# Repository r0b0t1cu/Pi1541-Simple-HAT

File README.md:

# Pi1541-Simple-HAT

An open-source Raspberry Pi HAT for the [Pi1541](https://github.com/pi1541/Pi1541) project — a cycle-exact emulator of the Commodore 1541 floppy disk drive. This board provides a clean, simple way to build a standalone Pi1541 unit with buttons, display, buzzer, and IEC connectivity, without needing to hand-wire everything on a breadboard.

---

## Overview

Pi1541 turns a Raspberry Pi into a hardware-accurate 1541 emulator that loads `.d64`, `.g64`, `.nib`, and other disk image formats from an SD card. This HAT breaks out everything you need onto a single board that sits directly on top of a Raspberry Pi 3B+.

The design is intentionally minimal — no SMD components beyond the connectors and passives, uses a widely available logic level converter module, and gives you flexibility on the IEC connector (DIN-6 socket or plain pin header, your choice).

---

## Features

- Designed as a standard 40-pin Raspberry Pi HAT
- Bidirectional logic level shifting (3.3V ↔ 5V) for the IEC bus
- Two IEC footprints: DIN-6 connector **or** pin header — populate whichever suits your build
- I2C connector for SSD1306 128×64 OLED display
- 5 navigation buttons: Select/Start, Up, Down, Exit Folder, Insert
- Reset button
- PWR and ACT indicator LEDs with current-limiting resistors
- Passive buzzer with enable/disable jumper (JP1)
- Voltage selector jumper (JP2): +5V or +3.3V for the display
- 4 mounting holes

---

## Hardware

### Bill of Materials

| Ref | Qty | Component | Description |
|-----|-----|-----------|-------------|
| U1 | 1 | SparkFun BOB-12009 (or equivalent) | Bidirectional logic level converter, BSS138-based, 4-channel |
| J1 | 1 | 40-pin female GPIO header | Standard 2.54mm pitch Raspberry Pi header |
| J3 | 1 | DIN-6 female socket **or** 6-pin header | IEC bus connector (primary) |
| J4 | 1 | DIN-6 female socket **or** 6-pin header | IEC bus connector (secondary footprint, same bus) |
| CN1 | 1 | 4-pin header | I2C display connector (GND, VCC, SCL, SDA) |
| SW1–SW5 | 5 | Tactile push button | Navigation: Select/Start, Up, Down, Exit Folder, Insert |
| SW6 | 1 | Tactile push button | Reset |
| LS1 | 1 | Passive buzzer | 5V passive buzzer |
| D1 | 1 | LED | ACT indicator |
| D2 | 1 | LED | PWR indicator |
| R1, R2 | 2 | Resistor | LED current limiting (value depends on LED and supply voltage) |
| JP1 | 1 | 2-pin jumper | Buzzer enable/disable |
| JP2 | 1 | 3-pin jumper | Voltage selector jumper (JP2): +5V or +3.3V for the display |

> **Note on IEC connectors:** J3 and J4 share the same electrical connection. You only need to populate one. Use a DIN-6 socket for a clean build, or a pin header if you want to use a cable with bare ends.

### Display

Connect any **SSD1306-based 128×64 OLED** (I2C, 4-pin: VCC/GND/SCL/SDA) to the I2C Display Connector. These are widely available and inexpensive.

### Level Shifter

The board uses a **4-channel bidirectional logic level converter** module (SparkFun BOB-12009 or any compatible clone based on the BSS138 MOSFET). This shifts the IEC bus signals between the Raspberry Pi's 3.3V GPIO and the 5V IEC bus.

---

## Software

This HAT runs the **Pi1541** firmware by Steve White. You do not need to compile anything — grab the pre-built release and follow the setup below.

### What to put on the SD card

1. Download the latest Pi1541 release from the official repository:
   👉 [https://github.com/pi1541/Pi1541](https://github.com/pi1541/Pi1541)

2. Format a microSD card as **FAT32**.

3. Copy the Pi1541 release files to the root of the SD card.

4. Copy the **`options.txt`** file from this repository to the root of the SD card (it contains the correct GPIO pin mapping and display configuration for this HAT).

5. Add your disk images (`.d64`, `.g64`, `.nib`, `.tap`, etc.) to the SD card — you can organise them in folders.

6. Insert the SD card into the Raspberry Pi, fit the HAT, and power on.

---

If you enjoy my projects and would like to support my work, you can do so through PCBWay. You can also order the PCBs for this project directly from the link below. Every bit of support is appreciated!

<p>
  
</p>

---

## Building the PCB

1. **Order the PCB** — use the Gerber files in `gerbers/`. Standard 2-layer 1.6mm FR4 works fine. PCBWay, JLCPCB and similar services all work.
2. **Solder passives first** — resistors, jumper headers.
3. **Solder the GPIO header** — use a 40-pin female header so the HAT sits on top of the Pi.
4. **Solder the level shifter module** — pin headers on both sides, fits into the U1 footprint.
5. **Solder buttons, LEDs, buzzer, and IEC connector(s)**.
6. **Fit the OLED** — connect via the I2C header with a short 4-wire cable.

---

## Compatibility

| Hardware | Status |
|----------|--------|
| Raspberry Pi 3B+ | ✅ Tested |
| Raspberry Pi 3B | ⚠️ Should work, not tested |
| Raspberry Pi Zero 2W | ⚠️ Should work, not tested |
| Raspberry Pi 4 | ⚠️ May work with Pi1541, not tested |

The Pi1541 firmware is timing-critical and works best on a **Raspberry Pi 3B+**. Other models may work but are not guaranteed.

---

## License

This project is open-source hardware released under the [CERN Open Hardware Licence v2 - Permissive (CERN-OHL-P)](https://ohwr.org/cern_ohl_p_v2.txt).

The Pi1541 firmware is the work of Steve White and is licensed separately — see the [Pi1541 repository](https://github.com/pi1541/Pi1541) for details.

---

## Author

Designed by [r0b0t1cu](https://github.com/r0b0t1cu) — 2026

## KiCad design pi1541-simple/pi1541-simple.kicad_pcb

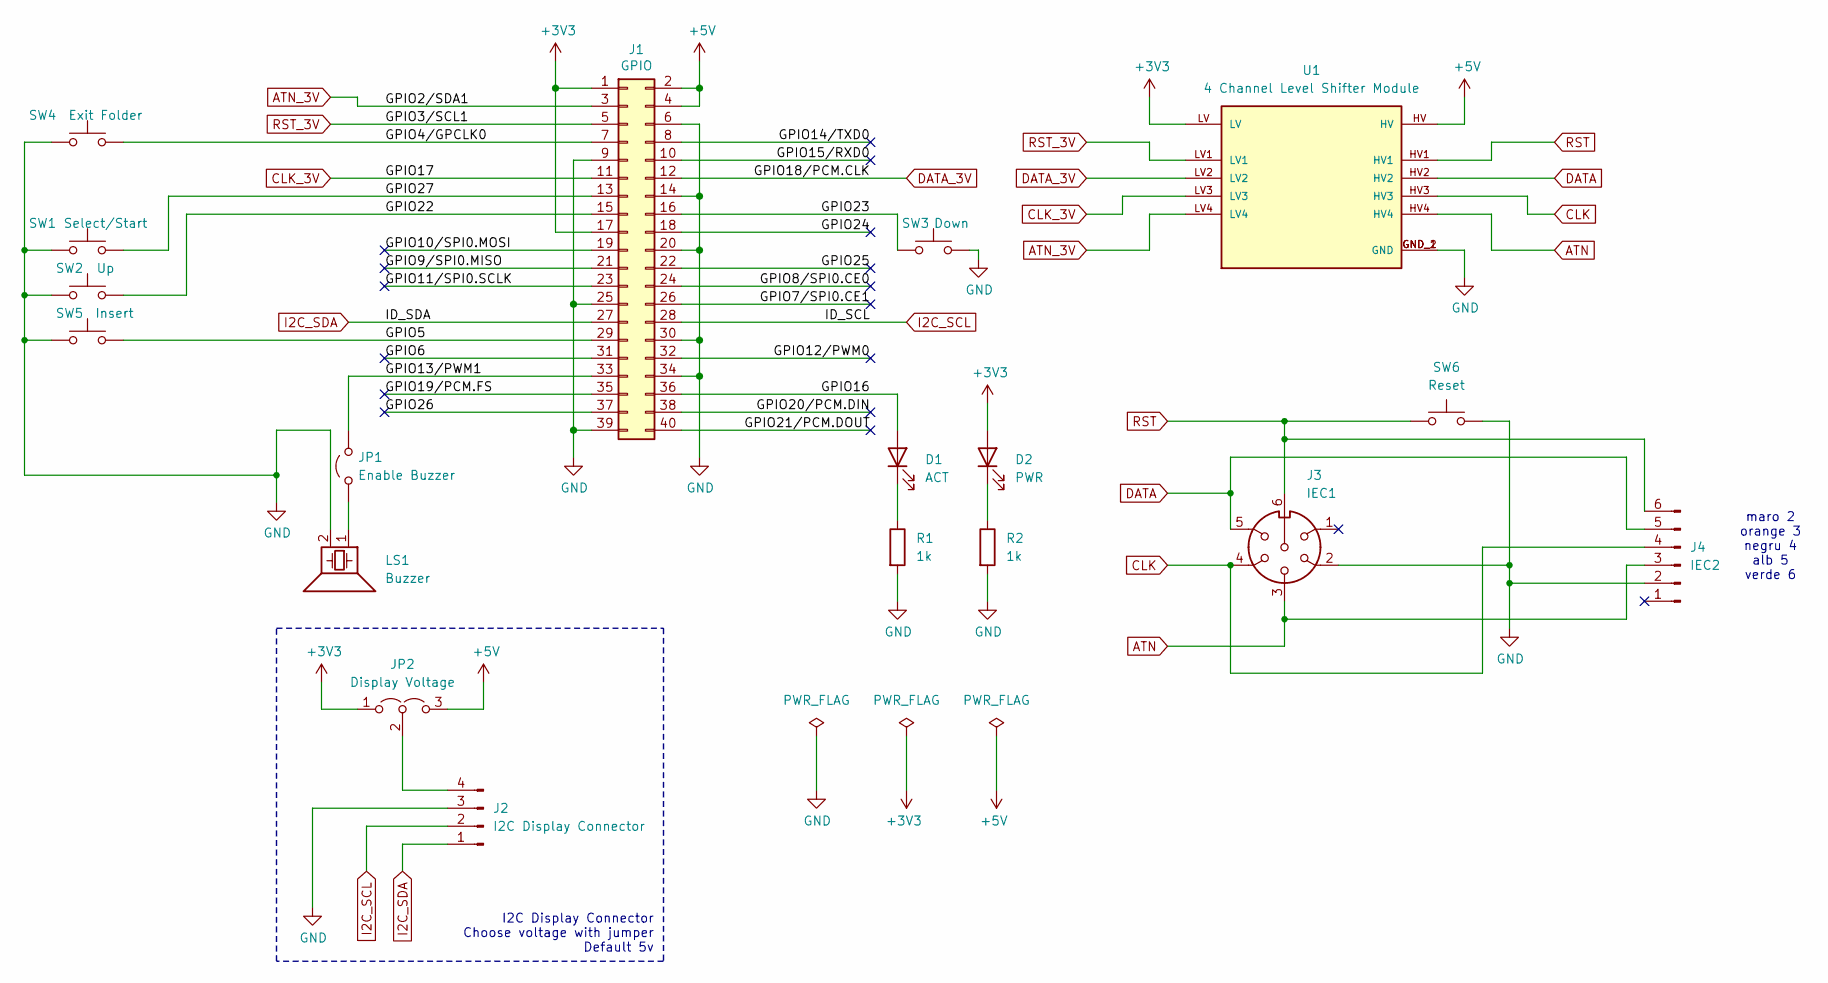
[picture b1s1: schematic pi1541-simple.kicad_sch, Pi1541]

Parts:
D1: ACT; LED_D3.0mm
D2: PWR; LED_D3.0mm
J1: GPIO; PinSocket_2x20_P2.54mm_Vertical
J2: I2C Display Connector; PinHeader_1x04_P2.54mm_Vertical
J3: IEC1; DIN-6
J4: IEC2; PinHeader_1x06_P2.54mm_Vertical
JP1: Enable Buzzer; PinHeader_1x02_P2.54mm_Vertical
JP2: Display Voltage; PinHeader_1x03_P2.54mm_Vertical
LS1: Buzzer; Buzzer_D14mm_H7mm_P10mm
R1, R2: 1k; R_Axial_DIN0207_L6.3mm_D2.5mm_P10.16mm_Horizontal
SW1: Select/Start; SW_Tactile_SPST_Angled_PTS645Vx83-2LFS
SW2: Up; SW_Tactile_SPST_Angled_PTS645Vx83-2LFS
SW3: Down; SW_Tactile_SPST_Angled_PTS645Vx83-2LFS
SW4: Exit Folder; SW_Tactile_SPST_Angled_PTS645Vx83-2LFS
SW5: Insert; SW_Tactile_SPST_Angled_PTS645Vx83-2LFS
SW6: Reset; SW_PUSH_6mm
U1: 4 Channel Level Shifter Module; CONV_BOB-12009; PARTREV 01

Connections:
+3V3: D2.2 (A), J1.1, J1.17, JP2.1 (A), U1.LV
+5V: J1.2, J1.4, JP2.3 (B), U1.HV
/GPIO4/GPCLK0: J1.7, SW4.2
/GPIO5: J1.29, SW5.2
/GPIO6: J1.31
/GPIO7/SPI0.CE1: J1.26
/GPIO8/SPI0.CE0: J1.24
/GPIO9/SPI0.MISO: J1.21
/GPIO10/SPI0.MOSI: J1.19
/GPIO11/SPI0.SCLK: J1.23
/GPIO12/PWM0: J1.32
/GPIO13/PWM1: J1.33, JP1.2 (B)
/GPIO14/TXD0: J1.8
/GPIO15/RXD0: J1.10
/GPIO16: D1.2 (A), J1.36
/GPIO19/PCM.FS: J1.35
/GPIO20/PCM.DIN: J1.38
/GPIO21/PCM.DOUT: J1.40
/GPIO22: J1.15, SW2.2
/GPIO23: J1.16, SW3.1
/GPIO24: J1.18
/GPIO25: J1.22
/GPIO26: J1.37
/GPIO27: J1.13, SW1.2
ATN: J3.3, J4.3, U1.HV4
ATN_3V: J1.3, U1.LV4
CLK: J3.4, J4.4, U1.HV3
CLK_3V: J1.11, U1.LV3
DATA: J3.5, J4.5, U1.HV2
DATA_3V: J1.12, U1.LV2
GND: J1.6, J1.9, J1.14, J1.20, J1.25, J1.30, J1.34, J1.39, J2.3, J3.2, J4.2, LS1.2, R1.2, R2.2, SW1.1, SW2.1, SW3.2, SW4.1, SW5.1, SW6.2, U1.GND_1 (GND), U1.GND_2 (GND)
I2C_SCL: J1.28, J2.2
I2C_SDA: J1.27, J2.1
unnamed: D1.1 (K), R1.1
unnamed: D2.1 (K), R2.1
unnamed: J2.4, JP2.2 (C)
unnamed: JP1.1 (A), LS1.1
RST: J3.6, J4.6, SW6.1, U1.HV1
RST_3V: J1.5, U1.LV1

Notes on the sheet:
I2C Display Connector Choose voltage with jumper Default 5v
maro 2 orange 3 negru 4 alb 5 verde 6

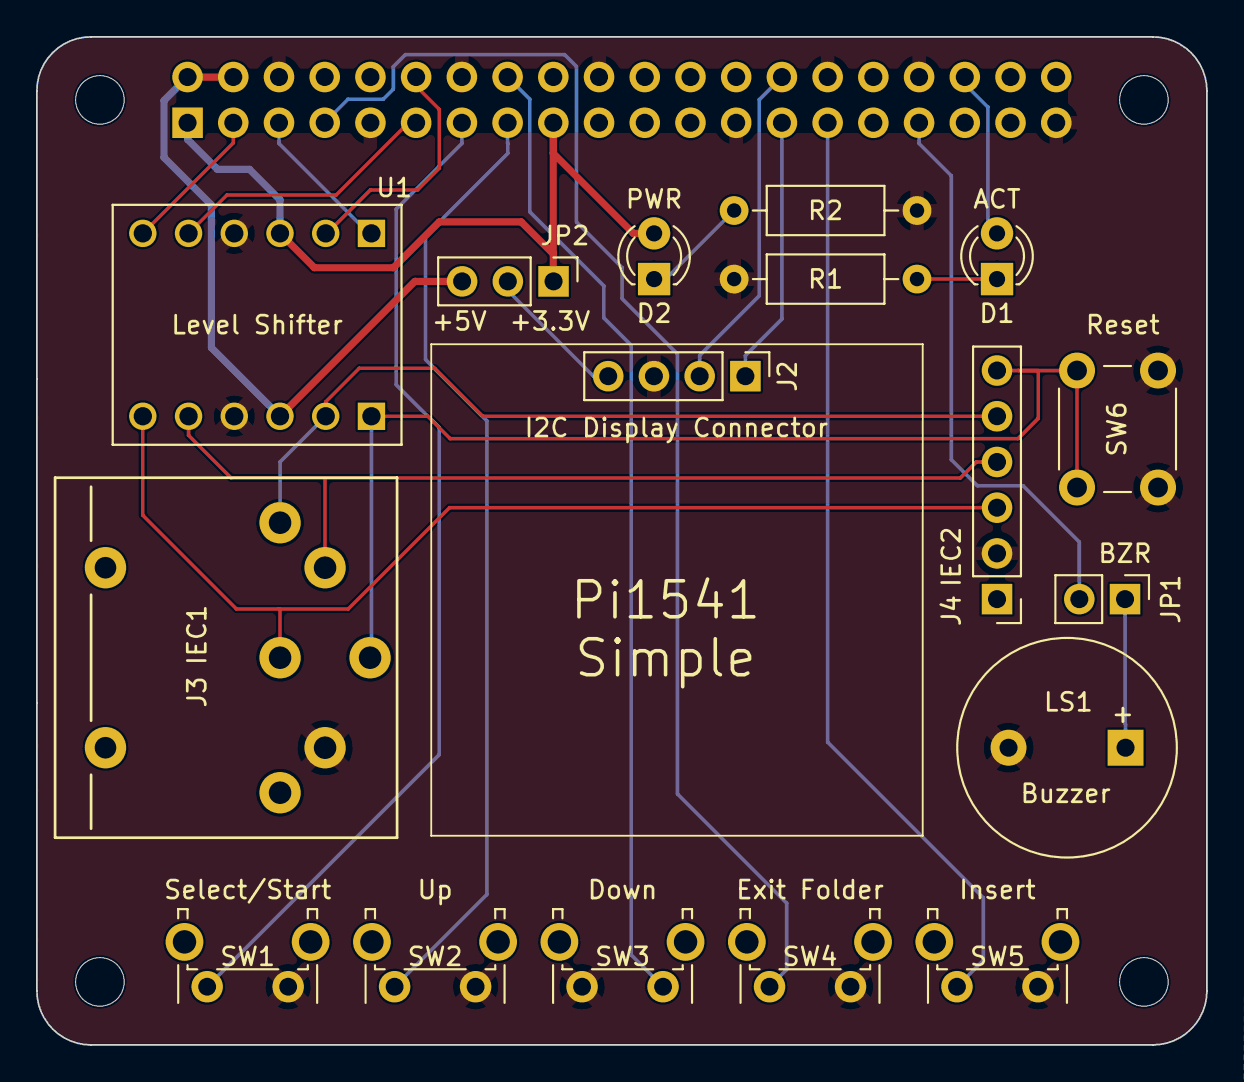
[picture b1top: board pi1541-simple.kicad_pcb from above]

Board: 2 copper layers, 65.0 x 56.0 mm, 22 parts (1 on the bottom side), 24 nets.

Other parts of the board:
MH1, MH2, MH3, MH4: MountingHole_2.7mm_M2.5

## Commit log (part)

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2026-05-07 Create README.md for Pi1541-Simple-HAT
    Add README for Pi1541-Simple-HAT project with details on features, hardware, software setup, and compatibility.
